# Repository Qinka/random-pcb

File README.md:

# random-pcb
The collection for PCB

## obj/89

Some button and LED for STM32f103 as expansion board.

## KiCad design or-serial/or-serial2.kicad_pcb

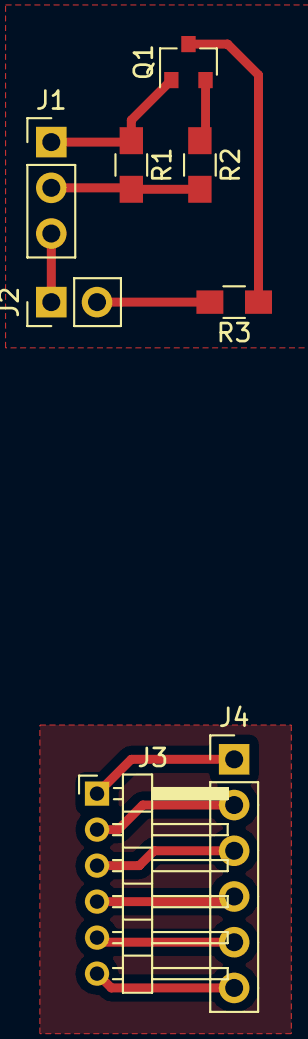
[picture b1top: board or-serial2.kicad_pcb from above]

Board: 2 copper layers, 8 parts (0 on the bottom side), 12 nets.

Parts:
J1: Conn_01x03_Male; Pin_Header_Straight_1x03_Pitch2.54mm
J2: Conn_01x02_Female; Socket_Strip_Straight_1x02_Pitch2.54mm
J3: Conn_01x06_Male; Pin_Header_Angled_1x06_Pitch2.00mm
J4: Conn_01x06_Male; Pin_Header_Straight_1x06_Pitch2.54mm
Q1: S8550; SOT-23
R1, R2, R3: R; R_0805_HandSoldering

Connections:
unnamed: J1.1, Q1.1, R1.1
unnamed: J1.2, R1.2, R2.2
unnamed: J1.3, J2.1
unnamed: J2.2, R3.2
unnamed: J3.1, J4.1
unnamed: J3.2, J4.2
unnamed: J3.3, J4.3
unnamed: J3.4, J4.4
unnamed: J3.5, J4.5
unnamed: J3.6, J4.6
unnamed: Q1.2, R2.1
unnamed: Q1.3, R3.1

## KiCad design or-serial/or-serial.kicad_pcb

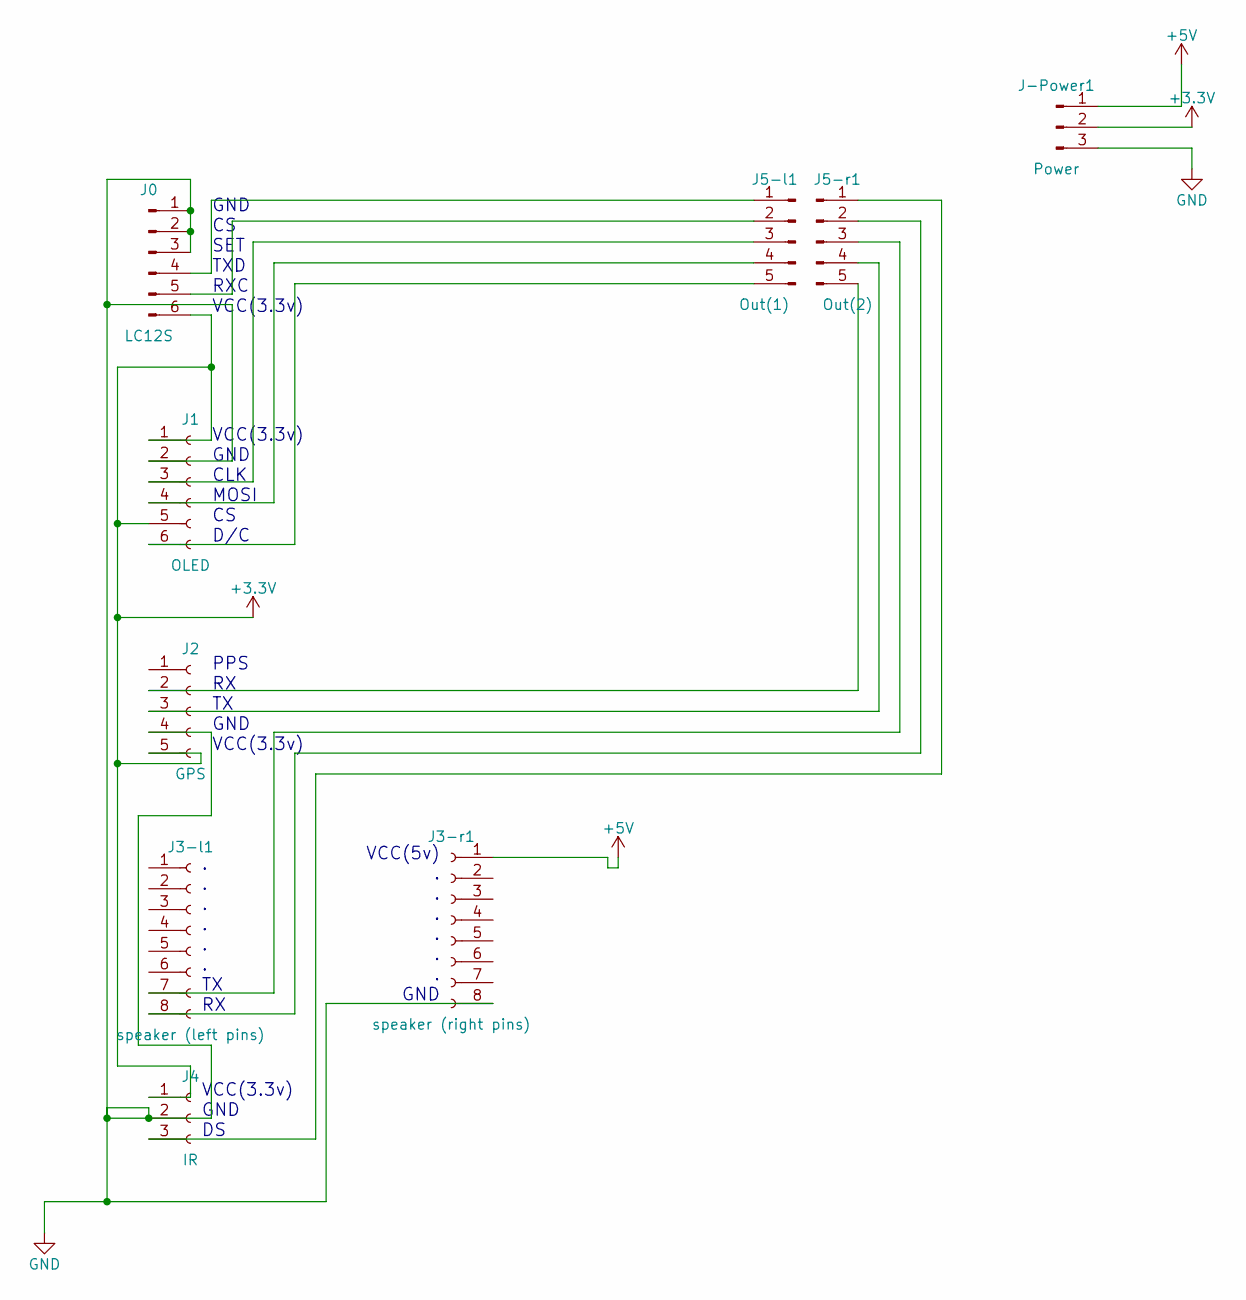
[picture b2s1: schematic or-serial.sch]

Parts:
J0: LC12S; Pin_Header_Angled_1x06_Pitch2.00mm
J1: OLED; Socket_Strip_Straight_1x06_Pitch2.54mm
J2: GPS; Socket_Strip_Straight_1x05_Pitch2.54mm
J3-l1: speaker (left pins); Socket_Strip_Straight_1x08_Pitch2.54mm
J3-r1: speaker (right pins); Socket_Strip_Straight_1x08_Pitch2.54mm
J4: IR; Socket_Strip_Straight_1x03_Pitch2.54mm
J5-l1: Out(1); Pin_Header_Straight_1x05_Pitch2.54mm
J5-r1: Out(2); Pin_Header_Straight_1x05_Pitch2.54mm
J-Power1: Power; Pin_Header_Straight_1x03_Pitch2.54mm

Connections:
+3V3: J0.6, J1.1, J1.5, J2.5, J4.1, J-Power1.2
+5V: J3-r1.1, J-Power1.1
GND: J0.1, J0.2, J0.3, J1.2, J2.4, J3-r1.8, J4.2, J-Power1.3
unnamed: J0.4, J5-l1.1
unnamed: J0.5, J5-l1.2
unnamed: J1.3, J5-l1.3
unnamed: J1.4, J5-l1.4
unnamed: J1.6, J5-l1.5
unnamed: J2.2, J5-r1.5
unnamed: J2.3, J5-r1.4
unnamed: J3-l1.7, J5-r1.3
unnamed: J3-l1.8, J5-r1.2
unnamed: J4.3, J5-r1.1

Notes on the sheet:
GND CS SET TXD RXC VCC(3.3v)
VCC(3.3v) GND CLK MOSI CS D/C
PPS RX TX GND VCC(3.3v)
. . . . . . TX RX
VCC(5v) . . . . . . GND
VCC(3.3v) GND DS

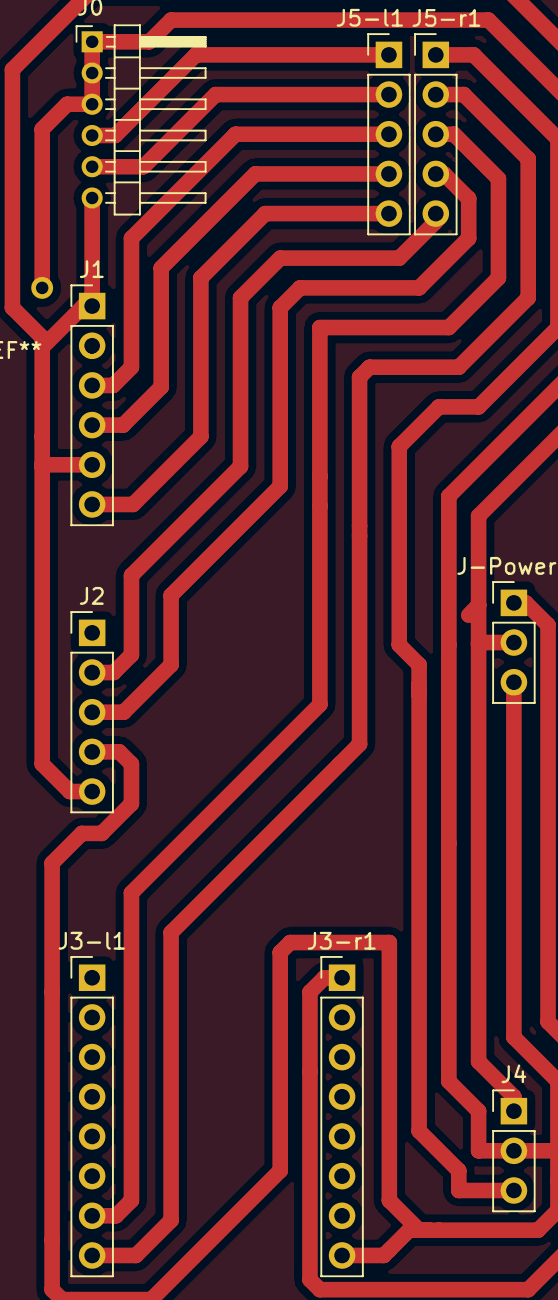
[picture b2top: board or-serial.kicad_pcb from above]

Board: 2 copper layers, 9 parts (0 on the bottom side), 13 nets.

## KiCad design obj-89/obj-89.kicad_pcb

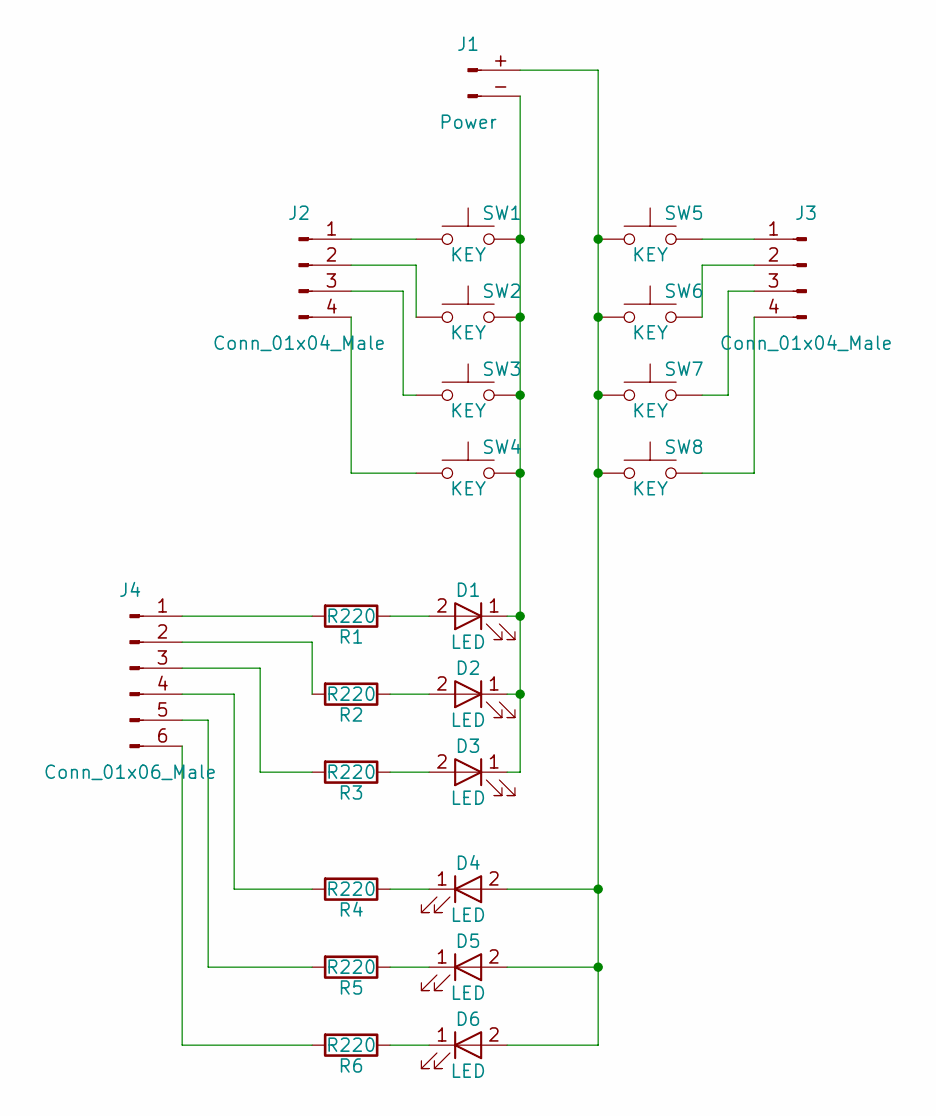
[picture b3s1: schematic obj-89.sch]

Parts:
D1, D2, D3, D4, D5, D6: LED; LED_D5.0mm
J1: Power; Pin_Header_Straight_1x02_Pitch2.54mm
J2, J3: Conn_01x04_Male; Pin_Header_Straight_1x04_Pitch2.54mm
J4: Conn_01x06_Male; Pin_Header_Straight_1x06_Pitch2.54mm
R1, R2, R3, R4, R5, R6: R220; R_Axial_DIN0207_L6.3mm_D2.5mm_P7.62mm_Horizontal
SW1, SW2, SW3, SW4, SW5, SW6, SW7, SW8: KEY; SW_PUSH_6mm

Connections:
unnamed: D1.1 (K), D2.1 (K), D3.1 (K), J1.- (Pin_2), SW1.2, SW2.2, SW3.2, SW4.2
unnamed: D1.2 (A), R1.1
unnamed: D2.2 (A), R2.1
unnamed: D3.2 (A), R3.1
unnamed: D4.1 (K), R4.1
unnamed: D4.2 (A), D5.2 (A), D6.2 (A), J1.+ (Pin_1), SW5.1, SW6.1, SW7.1, SW8.1
unnamed: D5.1 (K), R5.1
unnamed: D6.1 (K), R6.1
unnamed: J2.1, SW1.1
unnamed: J2.2, SW2.1
unnamed: J2.3, SW3.1
unnamed: J2.4, SW4.1
unnamed: J3.1, SW5.2
unnamed: J3.2, SW6.2
unnamed: J3.3, SW7.2
unnamed: J3.4, SW8.2
unnamed: J4.1, R1.2
unnamed: J4.2, R2.2
unnamed: J4.3, R3.2
unnamed: J4.4, R4.2
unnamed: J4.5, R5.2
unnamed: J4.6, R6.2

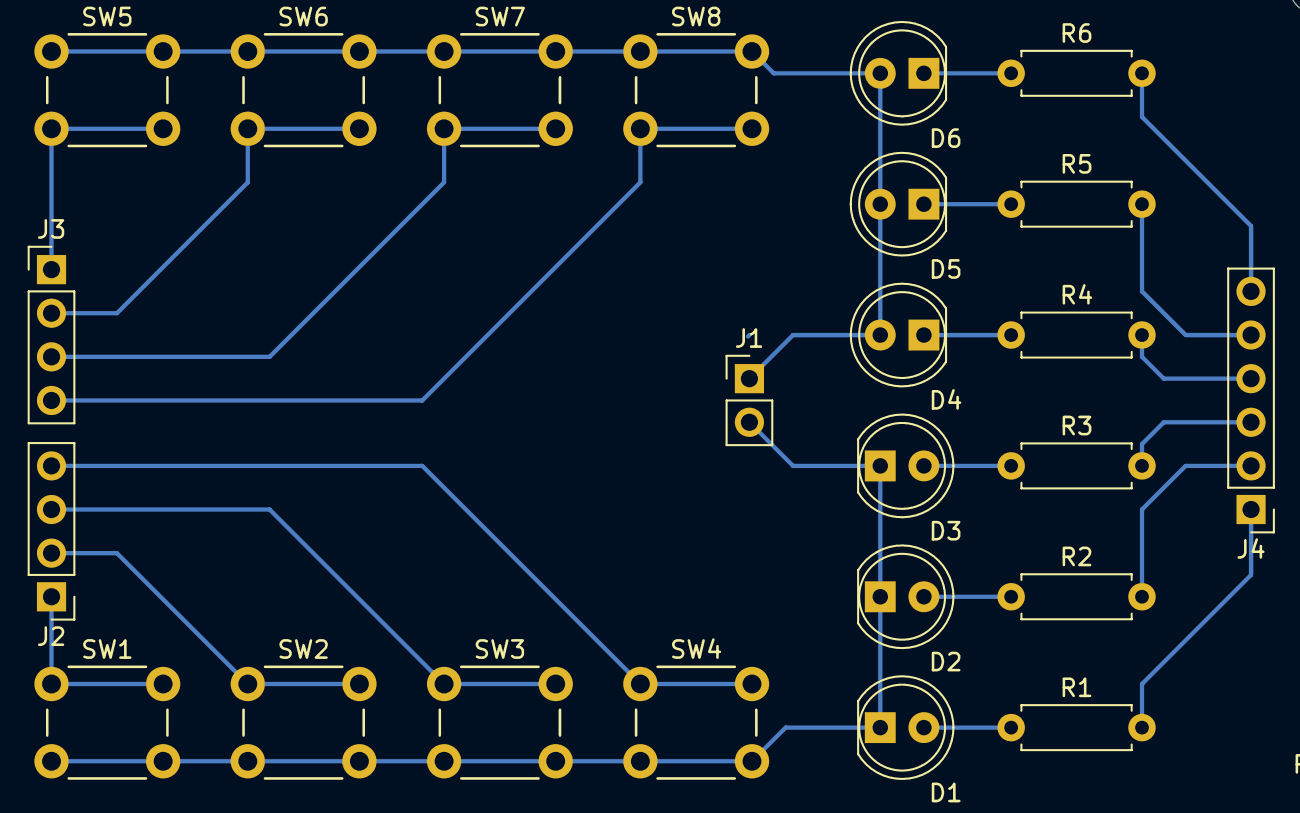
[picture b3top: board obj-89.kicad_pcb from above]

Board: 2 copper layers, 28 parts (0 on the bottom side), 22 nets.

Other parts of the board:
REF: MountingHole_3.2mm_M3
REF#2, REF#3, REF#4: MountingHole_3.2mm_M3

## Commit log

2017-10-03 update;
2017-10-03 add;
2017-10-03 add;update
2017-10-04 update
    unfinish
2017-10-09 update&add
    add pcb
2017-10-09 re-update
2017-10-14 add or-serial2
